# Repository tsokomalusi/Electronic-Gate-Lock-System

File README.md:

# Electronic-Gate-Lock-System

## Schematic capture

## 4-Layer PCB Layout

## 3D Model

## Block Diagram

## Fabricated PCB

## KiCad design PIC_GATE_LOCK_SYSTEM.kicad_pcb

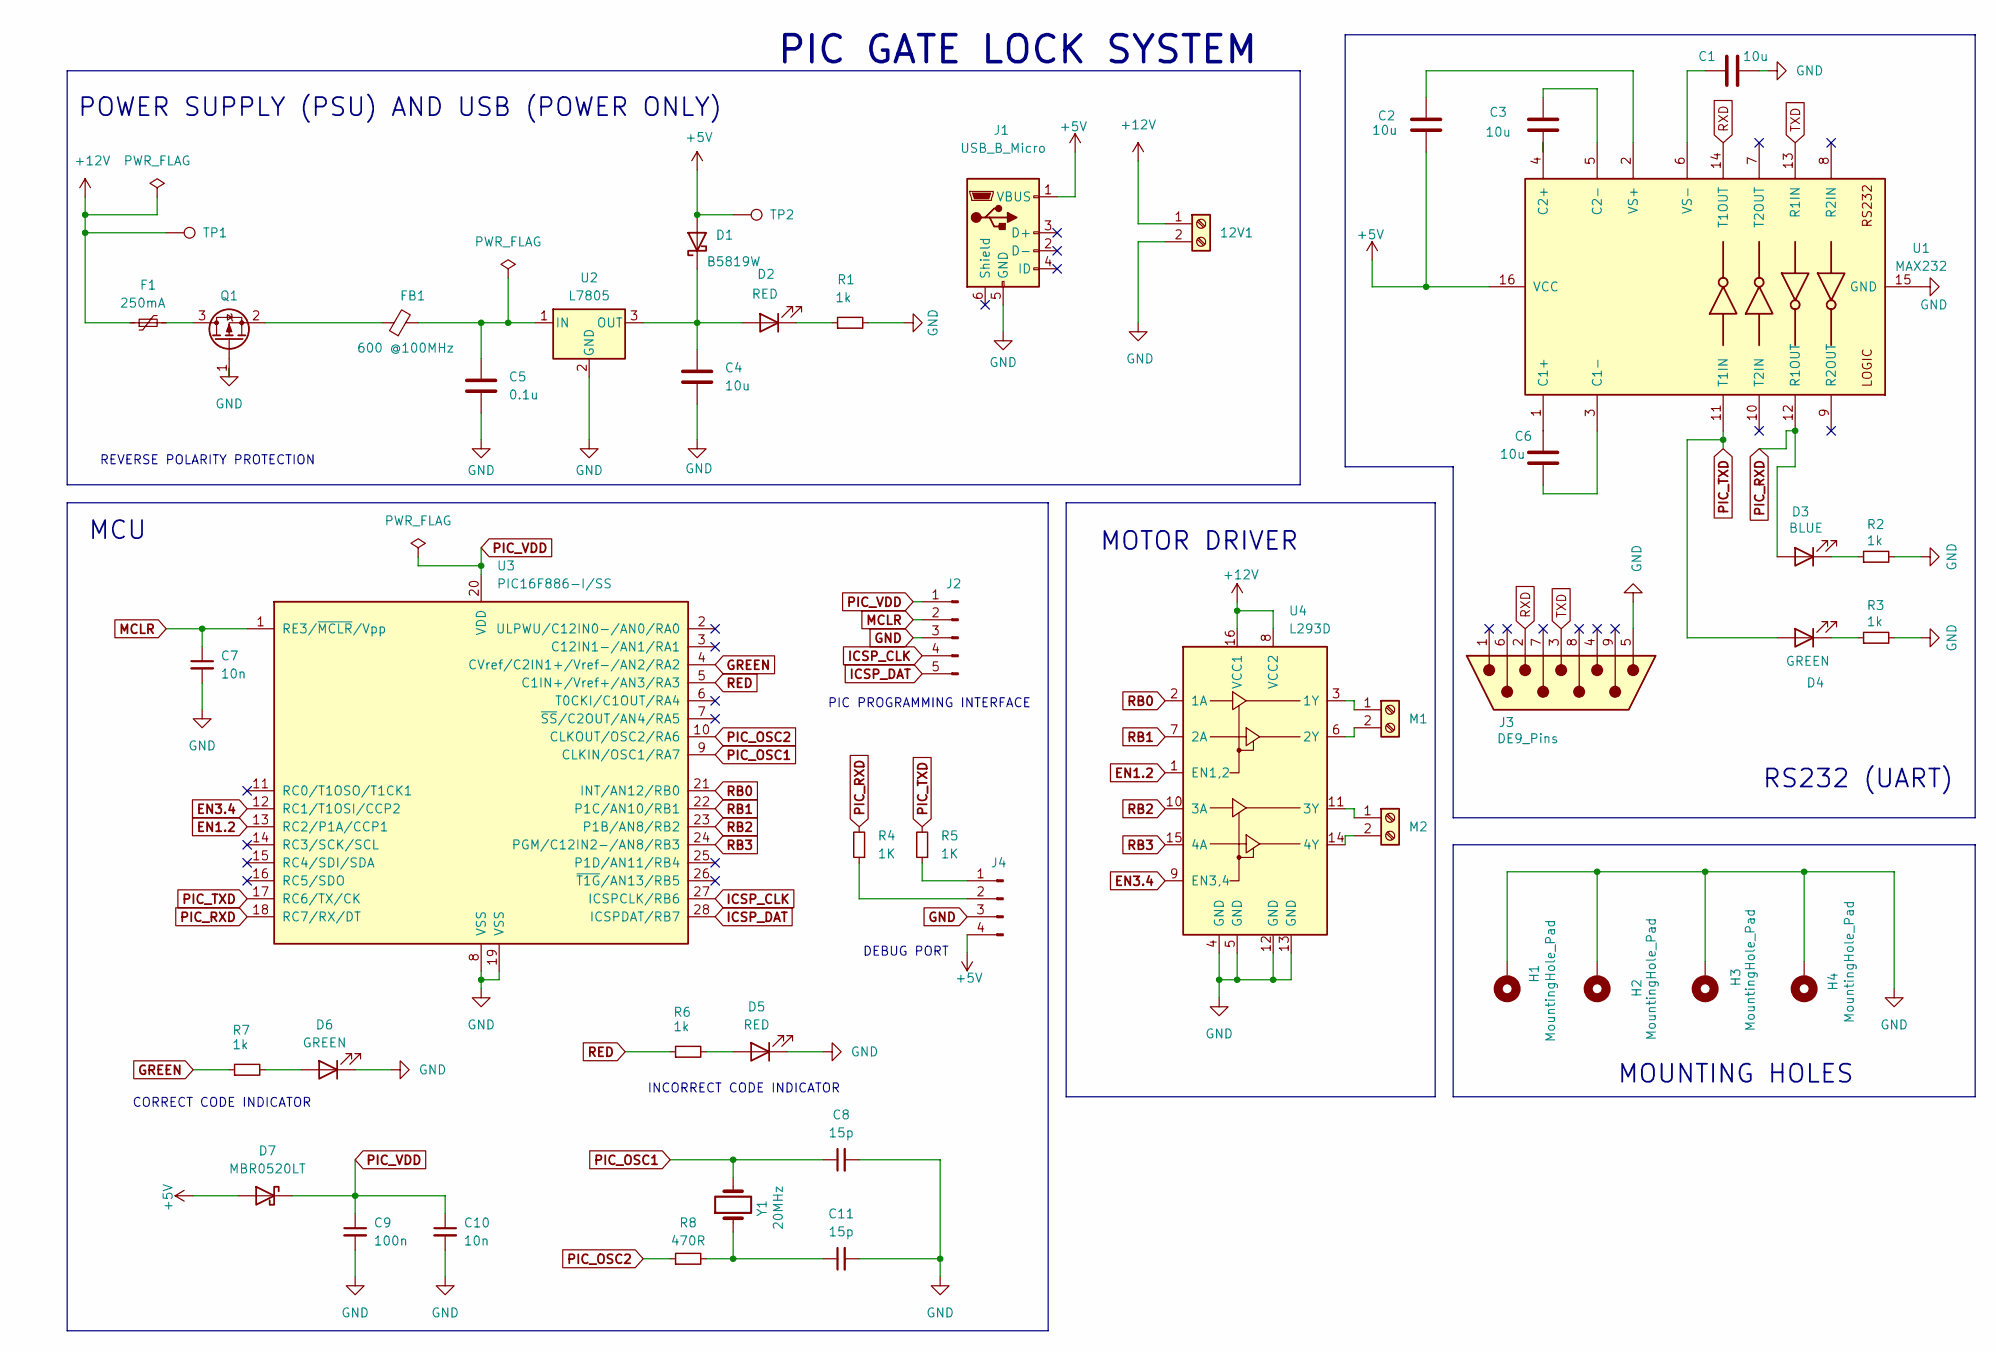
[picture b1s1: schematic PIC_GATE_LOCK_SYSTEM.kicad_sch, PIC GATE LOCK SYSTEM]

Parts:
12V1: Screw_Terminal_01x02; 691137710002
C1, C2, C3, C6: 10u; C_0603_1608Metric
C4: 10u; C_1206_3216Metric
C5: 0.1u; C_1206_3216Metric
C7, C10: 10n; C_0402_1005Metric
C8, C11: 15p; C_0402_1005Metric
C9: 100n; C_0402_1005Metric
D1: B5819W; D_SOD-123
D2, D5: RED; LED_0603_1608Metric
D3: BLUE; LED_0603_1608Metric
D4, D6: GREEN; LED_0603_1608Metric
D7: MBR0520LT; D_SOD-123
F1: 250mA; Fuse_1206_3216Metric
FB1: 600 @100MHz; L_0805_2012Metric
H1, H2, H3, H4: MountingHole_Pad; MountingHole_4.3mm_M4_Pad_Via
J1: USB_B_Micro; USB_Micro-B_Wuerth_629105150521
J2: Conn_01x05_Pin; PinHeader_1x05_P2.54mm_Vertical
J3: DE9_Pins; A-DF_09_A_KG-T4S
J4: Conn_01x04_Pin; PinHeader_1x04_P2.54mm_Vertical
M1, M2: Screw_Terminal_01x02; 691137710002
Q1: AO3401A; SOT-23
R1, R2, R3, R6, R7: 1k; R_0402_1005Metric
R4, R5: 1K; R_0402_1005Metric
R8: 470R; R_0402_1005Metric
TP1, TP2: TestPoint; TestPoint_Pad_D2.5mm
U1: MAX232; SOIC127P600X175-16N
U2: L7805; SOT-223
U3: PIC16F886-I/SS; SSOP28_MC_MCH
U4: L293D; SOIC127P1032X265-20N
Y1: 20MHz; XTAL_HC49P488W46L1150T500H350

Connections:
+5V: C2.1, D1.2 (A), D7.2 (A), J1.1 (VBUS), J4.4, TP2.1, U1.16 (VCC)
+12V: 12V1.1, F1.1, TP1.1, U4.8 (VCC2), U4.16 (VCC1)
EN1.2: U3.13 (RC2/P1A/CCP1), U4.1 (EN1,2)
EN3.4: U3.12 (RC1/T1OSI/CCP2), U4.9 (EN3,4)
GND: 12V1.2, C1.2, C4.2, C5.2, C7.2, C8.2, C9.2, C10.2, C11.2, D5.1 (K), D6.1 (K), H1.1, H2.1, H3.1, H4.1, J1.5 (GND), J2.3, J3.5, J4.3, Q1.1 (G), R1.2, R2.2, R3.2, U1.15 (GND), U2.2 (GND), U2.4, U3.8 (VSS), U3.19 (VSS), U4.4 (GND), U4.5 (GND), U4.12 (GND), U4.13 (GND)
GREEN: R7.1, U3.4 (CVref/C2IN1+/Vref-/AN2/RA2)
ICSP_CLK: J2.4, U3.27 (ICSPCLK/RB6)
ICSP_DAT: J2.5, U3.28 (ICSPDAT/RB7)
MCLR: C7.1, J2.2, U3.1 (RE3/~MCLR/Vpp)
unnamed: C11.1, R8.2, Y1.1
unnamed: C4.1, D1.1 (K), D2.2 (A), U2.3 (OUT)
unnamed: D2.1 (K), R1.1
unnamed 12: D3.1 (K), R2.1; also elsewhere on the board
unnamed 13: D4.1 (K), R3.1; also elsewhere on the board
unnamed: D5.2 (A), R6.2
unnamed: D6.2 (A), R7.2
unnamed: J4.1, R5.1
unnamed: J4.2, R4.1
unnamed: M1.1, U4.3 (1Y)
unnamed: M1.2, U4.6 (2Y)
unnamed: M2.1, U4.11 (3Y)
unnamed: M2.2, U4.14 (4Y)
unnamed: F1.2, Q1.3 (D)
unnamed: FB1.1, Q1.2 (S)
unnamed: C6.1, U1.1 (C1+)
unnamed: C6.2, U1.3 (C1-)
unnamed: C3.1, U1.4 (C2+)
unnamed: C3.2, U1.5 (C2-)
unnamed: C2.2, U1.2 (VS+)
unnamed: C1.1, U1.6 (VS-)
unnamed: C5.1, FB1.2, U2.1 (IN)
PIC_OSC1: C8.1, U3.9 (CLKIN/OSC1/RA7), Y1.2
PIC_OSC2: R8.1, U3.10 (CLKOUT/OSC2/RA6)
PIC_RXD: D3.2 (A), R4.2, U1.12 (R1OUT), U3.18 (RC7/RX/DT); also elsewhere on the board
PIC_TXD: D4.2 (A), R5.2, U1.11 (T1IN), U3.17 (RC6/TX/CK); also elsewhere on the board
PIC_VDD: C9.1, C10.1, D7.1 (K), J2.1, U3.20 (VDD)
RB0: U3.21 (INT/AN12/RB0), U4.2 (1A)
RB1: U3.22 (P1C/AN10/RB1), U4.7 (2A)
RB2: U3.23 (P1B/AN8/RB2), U4.10 (3A)
RB3: U3.24 (PGM/C12IN2-/AN8/RB3), U4.15 (4A)
RED: R6.1, U3.5 (C1IN+/Vref+/AN3/RA3)
RXD: J3.2, U1.14 (T1OUT)
TXD: J3.3, U1.13 (R1IN)

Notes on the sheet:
REVERSE POLARITY PROTECTION
PIC PROGRAMMING INTERFACE
MCU
DEBUG PORT
RS232 (UART)
PIC GATE LOCK SYSTEM
MOTOR DRIVER
POWER SUPPLY (PSU) AND USB (POWER ONLY)
INCORRECT CODE INDICATOR
MOUNTING HOLES
CORRECT CODE INDICATOR

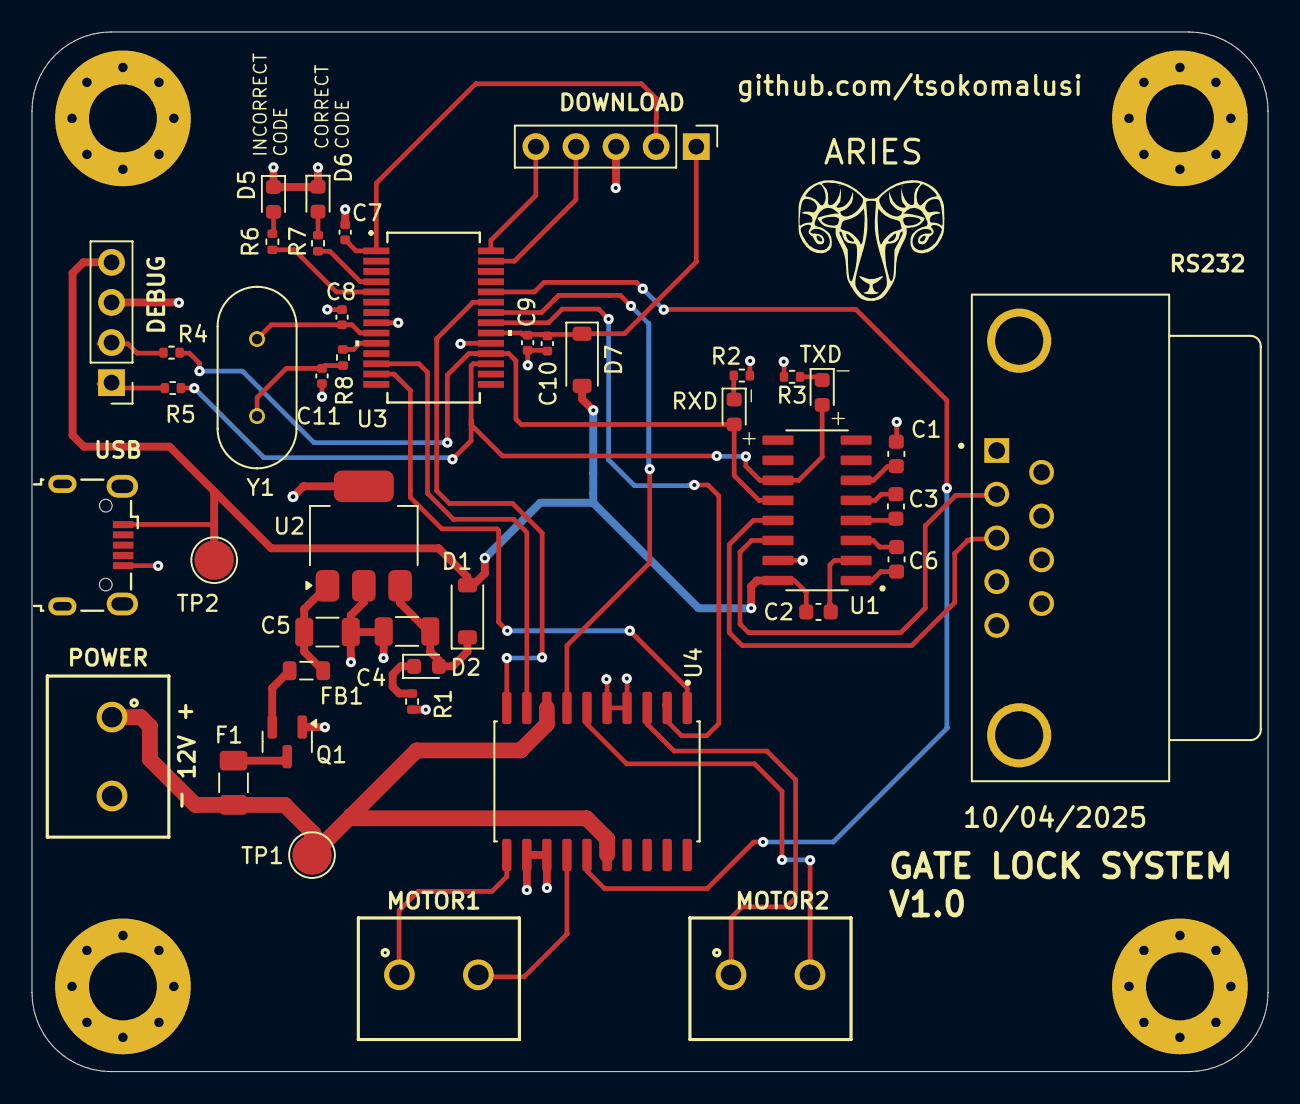
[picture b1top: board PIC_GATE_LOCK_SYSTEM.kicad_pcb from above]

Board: 4 copper layers, 78.3 x 65.8 mm, 47 parts (0 on the bottom side), 43 nets.

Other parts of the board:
RXD: BLUE; LED_0603_1608Metric
TXD: GREEN; LED_0603_1608Metric

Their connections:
unnamed 12: RXD.1 (K); also elsewhere on the board
unnamed 13: TXD.1 (K); also elsewhere on the board
PIC_RXD: RXD.2 (A); also elsewhere on the board
PIC_TXD: TXD.2 (A); also elsewhere on the board

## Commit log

2025-05-16 uploading project files
2025-05-17 Updated readme file
2025-05-17 added image directory
